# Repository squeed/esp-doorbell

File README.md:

#ESP-Doorbell.

I can't make copies of my apartment building's front door. However, the building
did kindly provide a pair of wires, where connecting one to the other unlocks
the door.

These wires happen to be inside the doorbell, but that's no big deal. The doorbell
has a special chassis for expansion boards!

So, in `/hardware` you'll see a schematic and board design that slots in to the
chassis.

In `/software` you'll find some fun things that will cause various requests to open the door.

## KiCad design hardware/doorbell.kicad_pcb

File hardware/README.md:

ESP8266 to Doorbell adapter
===========================

This is a simple PCB that connects an ESP-8266 with a Ritto 6630 door opener. This
sort of hardware is typically used in German apartment buildings. The circuit allows
the front door to be opened via an ESP8266.

This particular telephone has slots for multiple modules within the chassis. This board
is designed to fit in that slot.

The telephone opens the door by tying the Opener signal to Ground. So, this board
provides an optoisolator that simulates pressing the button. The opener signal
is somewhere around 8v, and draws about 12mA when grounded. It needs at least a
transistor for protection, but I'm interfacing via an optocoupler.

Since the system also supplies a 12v power rail, we use that too.

This also exposes the SPI lines to connect an LED strip, because those are useful.
The goal is to someday expose BVG timing on them.

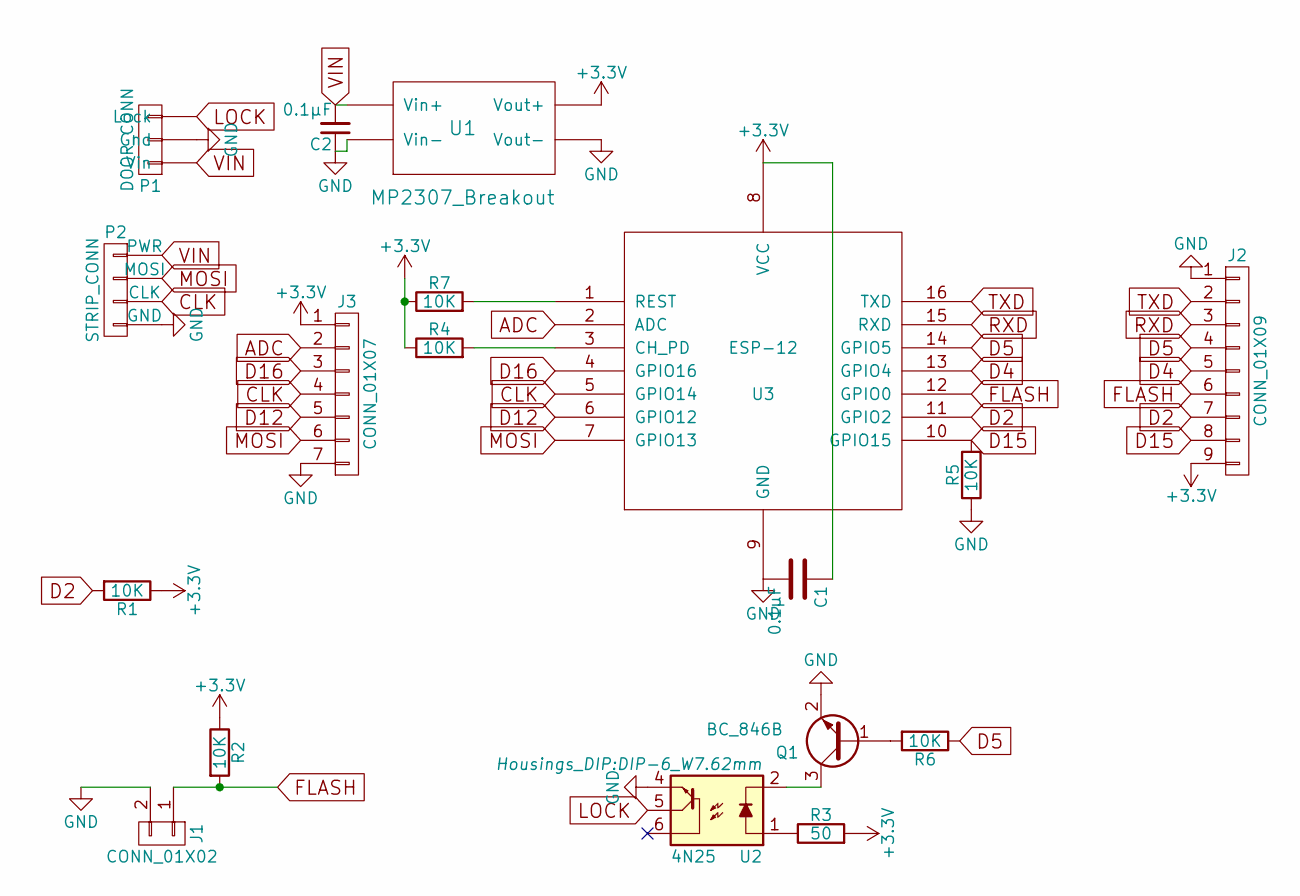
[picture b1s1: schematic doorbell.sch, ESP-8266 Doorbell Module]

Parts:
C1, C2: 0.1µF; C_1206_HandSoldering
J1: CONN_01X02; Pin_Header_Straight_1x02
J2: CONN_01X09; Pin_Header_Straight_1x09
J3: CONN_01X07; Pin_Header_Straight_1x07
P1: DOOR_CONN; TerminalBlock_Pheonix_MPT-2.54mm_3pol
P2: STRIP_CONN; TerminalBlock_Pheonix_MPT-2.54mm_4pol
Q1: BC_846B; SOT-23_Handsoldering
R1, R2, R4, R5, R6, R7: 10K; Resistor_Vertical_RM5mm
R3: 50; Resistor_Vertical_RM5mm
U1: MP2307_Breakout
U2: 4N25; DIP-6_W7.62mm
U3: ESP-12

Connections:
+3V3: C1.1, J2.9, J3.1, R1.1, R2.1, R3.2, R4.1, R7.1, U1.3 (Vout+), U3.8 (VCC)
ADC: J3.2, U3.2 (ADC)
CLK: J3.4, P2.3 (CLK), U3.5 (GPIO14)
D2: J2.7, R1.2, U3.11 (GPIO2)
D4: J2.5, U3.13 (GPIO4)
D5: J2.4, R6.1, U3.14 (GPIO5)
D12: J3.5, U3.6 (GPIO12)
D15: J2.8, R5.2, U3.10 (GPIO15)
D16: J3.3, U3.4 (GPIO16)
FLASH: J1.1, J2.6, R2.2, U3.12 (GPIO0)
GND: C1.2, C2.1, J1.2, J2.1, J3.7, P1.2 (Gnd), P2.4 (GND), Q1.2 (E), R5.1, U1.2 (Vin-), U1.4 (Vout-), U2.4, U3.9 (GND)
LOCK: P1.3 (Lock), U2.5
MOSI: J3.6, P2.2 (MOSI), U3.7 (GPIO13)
unnamed: Q1.1 (B), R6.2
unnamed: Q1.3 (C), U2.2
unnamed: R3.1, U2.1
unnamed: R4.2, U3.3 (CH_PD)
unnamed: R7.2, U3.1 (REST)
RXD: J2.3, U3.15 (RXD)
TXD: J2.2, U3.16 (TXD)
VIN: C2.2, P1.1 (Vin), P2.1 (PWR), U1.1 (Vin+)

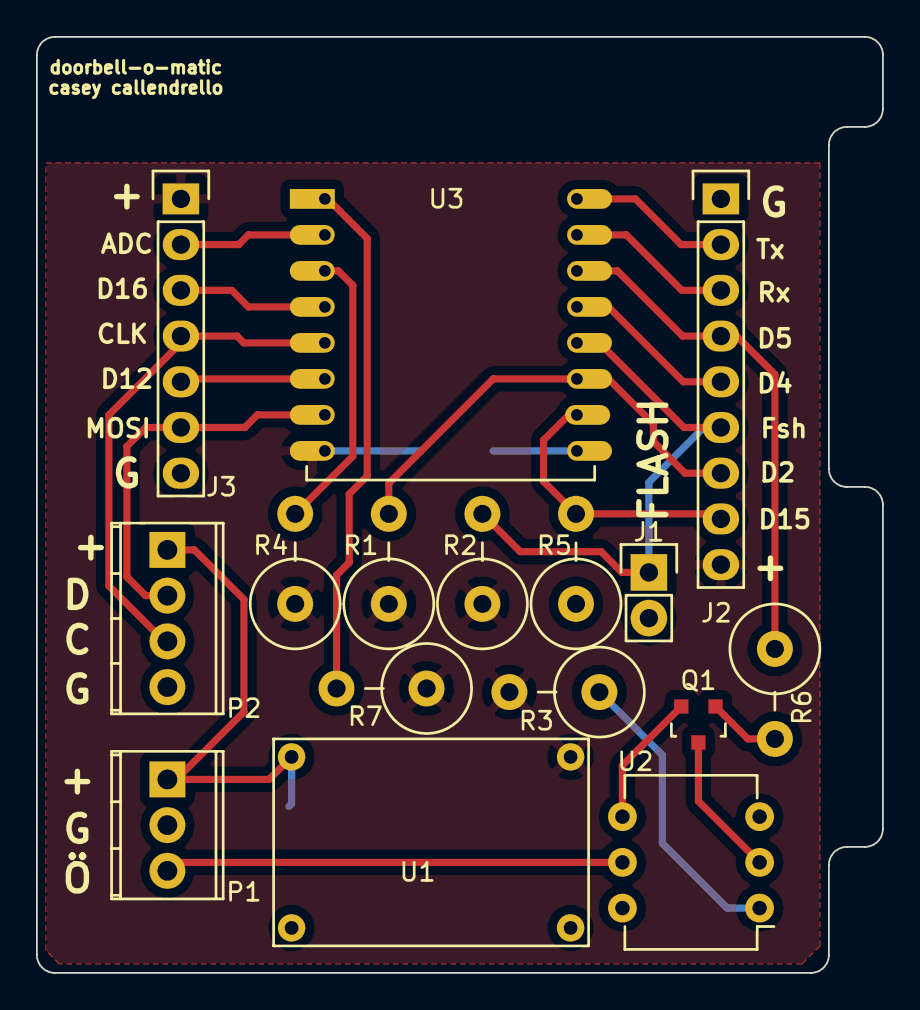
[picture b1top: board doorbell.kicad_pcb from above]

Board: 2 copper layers, 47.0 x 52.0 mm, 18 parts (0 on the bottom side), 21 nets.

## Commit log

2016-05-23 My first kicad design ever!
2016-05-23 Add image renders
2016-05-24 Fix some library issues
2016-05-24 Fix trace width, expand copper fills
2016-05-25 Shrink board, expand copper, change Q1 bom
2016-05-30 Convert to include a switching voltage regulator breakout
2016-05-30 Update renderings
2016-05-30 Add Vin decoupling cap
2016-05-30 Small text cleanups
2016-05-30 Final changes. This is the ordered version
